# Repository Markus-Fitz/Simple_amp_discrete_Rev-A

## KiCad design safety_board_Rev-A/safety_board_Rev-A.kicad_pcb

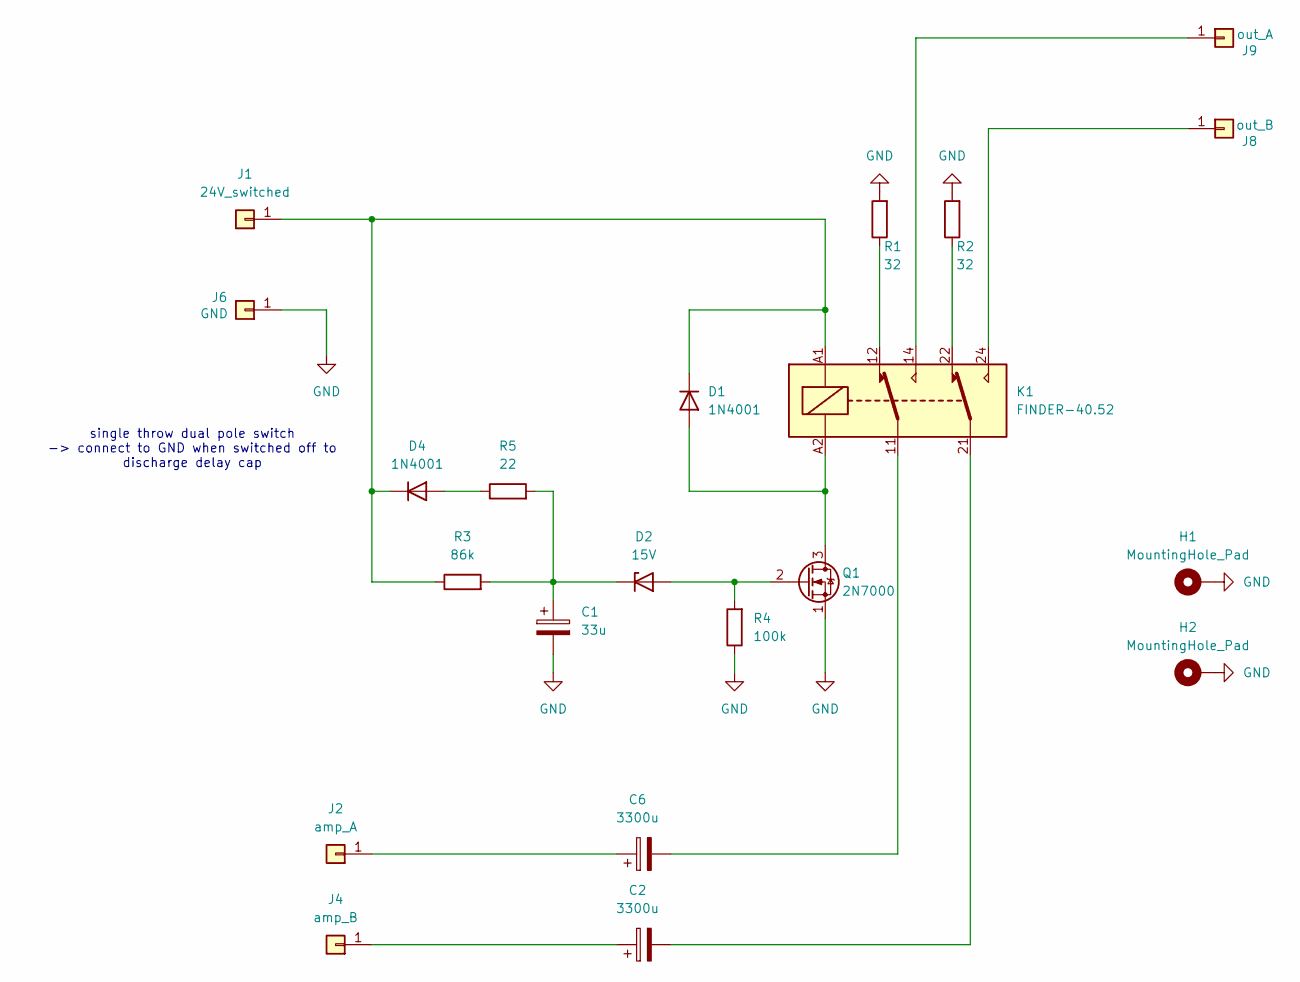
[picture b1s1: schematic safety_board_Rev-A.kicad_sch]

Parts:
C1: 33u; C_Radial_D8.0mm_H11.5mm_P3.50mm
C2, C6: 3300u; CP_Radial_D16.0mm_P7.50mm; MPN UFW1V332MHD
D1, D4: 1N4001; D_DO-41_SOD81_P10.16mm_Horizontal
D2: 15V; D_DO-35_SOD27_P7.62mm_Horizontal
H1, H2: MountingHole_Pad; MountingHole_3.2mm_M3_DIN965_Pad_TopBottom
J1: 24V_switched; TestPoint_THTPad_D3.0mm_Drill1.5mm
J2: amp_A; TestPoint_THTPad_D3.0mm_Drill1.5mm
J4: amp_B; TestPoint_THTPad_D3.0mm_Drill1.5mm
J6: GND; TestPoint_THTPad_D3.0mm_Drill1.5mm
J8: out_B; TestPoint_THTPad_D3.0mm_Drill1.5mm
J9: out_A; TestPoint_THTPad_D3.0mm_Drill1.5mm
K1: FINDER-40.52; Relay_DPDT_Finder_40.52
Q1: 2N7000; TO-92_Inline
R1, R2: 32; R_Axial_DIN0207_L6.3mm_D2.5mm_P10.16mm_Horizontal
R3: 86k; R_Axial_DIN0207_L6.3mm_D2.5mm_P10.16mm_Horizontal
R4: 100k; R_Axial_DIN0207_L6.3mm_D2.5mm_P10.16mm_Horizontal
R5: 22; R_Axial_DIN0207_L6.3mm_D2.5mm_P10.16mm_Horizontal

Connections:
GND: C1.2, H1.1, H2.1, J6.1, Q1.1 (S), R1.2, R2.2, R4.1
unnamed: C2.2, K1.21
unnamed: C6.2, K1.11
unnamed: D1.2 (A), K1.A2, Q1.3 (D)
unnamed: D1.1 (K), D4.1 (K), J1.1, K1.A1, R3.1
unnamed: D2.2 (A), Q1.2 (G), R4.2
unnamed: C1.1, D2.1 (K), R3.2, R5.2
unnamed: D4.2 (A), R5.1
unnamed: C6.1, J2.1
unnamed: C2.1, J4.1
unnamed: J8.1, K1.24
unnamed: J9.1, K1.14
unnamed: K1.12, R1.1
unnamed: K1.22, R2.1

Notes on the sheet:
single throw dual pole switch -> connect to GND when switched off to discharge delay cap

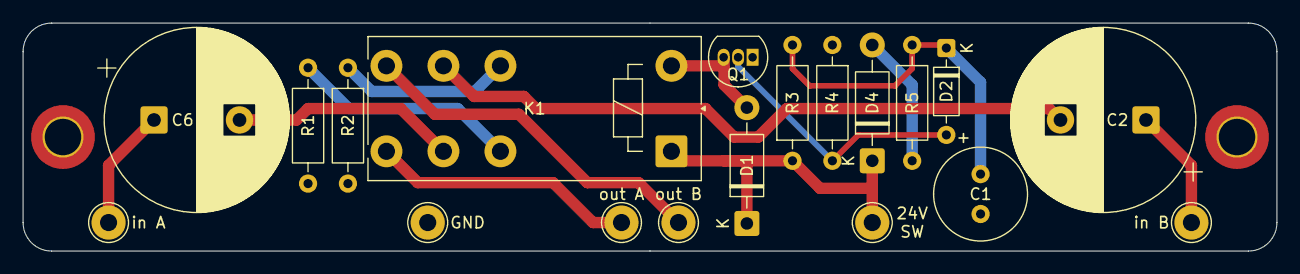
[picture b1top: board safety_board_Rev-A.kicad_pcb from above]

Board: 2 copper layers, 110.0 x 20.0 mm, 21 parts (0 on the bottom side), 14 nets.

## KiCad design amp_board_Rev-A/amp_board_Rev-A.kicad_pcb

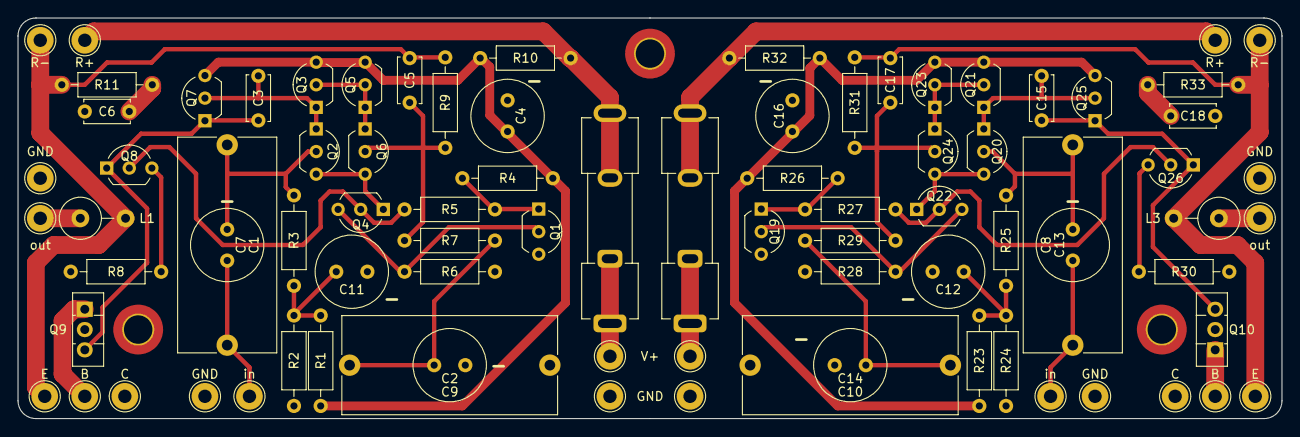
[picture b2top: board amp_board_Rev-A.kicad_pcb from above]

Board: 2 copper layers, 142.0 x 45.0 mm, 87 parts (0 on the bottom side), 41 nets.

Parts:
C1, C2, C4, C11, C12, C13, C14, C16: 33u; C_Radial_D8.0mm_H11.5mm_P3.50mm
C3, C15: 47p; C_Disc_D5.0mm_W2.5mm_P5.00mm
C5, C17: 3.3p; C_Disc_D5.0mm_W2.5mm_P5.00mm
C6, C18: C_sn; C_Disc_D5.0mm_W2.5mm_P5.00mm
C7, C8, C9, C10: 10u_foil; C_Rect_L24.0mm_W10.9mm_P22.50mm_MKT
F1, F2: 2A f; Fuseholder_Clip-5x20mm_Keystone_3512P_Inline_P23.62x7.27mm_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
H1, H2, H3: MountingHole_Pad; MountingHole_3.2mm_M3_DIN965_Pad_TopBottom
J1: in; TestPoint_THTPad_D3.0mm_Drill1.5mm
J2: R_power+; TestPoint_THTPad_D3.0mm_Drill1.5mm
J3: R_power-; TestPoint_THTPad_D3.0mm_Drill1.5mm
J4: MJ2955_E; TestPoint_THTPad_D3.0mm_Drill1.5mm
J5: MJ2955_B; TestPoint_THTPad_D3.0mm_Drill1.5mm
J6: MJ2955_C; TestPoint_THTPad_D3.0mm_Drill1.5mm
J7, J10: V+_in; TestPoint_THTPad_D3.0mm_Drill1.5mm
J8: out; TestPoint_THTPad_D3.0mm_Drill1.5mm
J9, J12: GND; TestPoint_THTPad_D3.0mm_Drill1.5mm
J11: in_GND; TestPoint_THTPad_D3.0mm_Drill1.5mm
J_B1: MJ2955_B; TestPoint_THTPad_D3.0mm_Drill1.5mm
J_C1: MJ2955_C; TestPoint_THTPad_D3.0mm_Drill1.5mm
J_E1: MJ2955_E; TestPoint_THTPad_D3.0mm_Drill1.5mm
J_GND1: in_GND; TestPoint_THTPad_D3.0mm_Drill1.5mm
J_GND2, J_GND3: out_GND; TestPoint_THTPad_D3.0mm_Drill1.5mm
J_R+1: R_power+; TestPoint_THTPad_D3.0mm_Drill1.5mm
J_R-1: R_power-; TestPoint_THTPad_D3.0mm_Drill1.5mm
J_in1: in; TestPoint_THTPad_D3.0mm_Drill1.5mm
J_out1: out; TestPoint_THTPad_D3.0mm_Drill1.5mm
L1, L3: 10u; L_Axial_L11.0mm_D4.5mm_P5.08mm_Vertical_Fastron_MECC
Q1, Q2, Q4, Q6, Q8, Q19, Q20, Q22, Q24, Q26: BC547; TO-92_Inline_Wide
Q3, Q5, Q7, Q21, Q23, Q25: BC557; TO-92_Inline_Wide
Q9, Q10: BD140; TO-126-3_Vertical
R1, R2, R23, R24: 4k7; R_Axial_DIN0207_L6.3mm_D2.5mm_P10.16mm_Horizontal
R3, R25: 42k; R_Axial_DIN0207_L6.3mm_D2.5mm_P10.16mm_Horizontal
R4, R26: 22k; R_Axial_DIN0207_L6.3mm_D2.5mm_P10.16mm_Horizontal
R5, R6, R27, R28: 1k; R_Axial_DIN0207_L6.3mm_D2.5mm_P10.16mm_Horizontal
R7, R29: 10k; R_Axial_DIN0207_L6.3mm_D2.5mm_P10.16mm_Horizontal
R8, R30: 330; R_Axial_DIN0207_L6.3mm_D2.5mm_P10.16mm_Horizontal
R9, R31: 47k; R_Axial_DIN0207_L6.3mm_D2.5mm_P10.16mm_Horizontal
R10, R32: 10; R_Axial_DIN0207_L6.3mm_D2.5mm_P10.16mm_Horizontal
R11, R33: R_sn; R_Axial_DIN0207_L6.3mm_D2.5mm_P10.16mm_Horizontal

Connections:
/channel_l/V+: F2.1, J7.1
/channel_l/V+_filt: C16.1, Q21.3 (E), Q23.3 (E), Q25.3 (E), R23.1, R26.2, R32.1
/channel_l/in+: C8.2, C13.2, Q20.2 (B), R25.2
/channel_l/in-: C17.1, Q24.2 (B), R29.1, R31.1
/channel_r/V+: F1.1, J10.1
/channel_r/V+_filt: C4.1, Q3.3 (E), Q5.3 (E), Q7.3 (E), R1.1, R4.2, R10.1
/channel_r/in+: C1.2, C7.2, Q2.2 (B), R3.2
/channel_r/in-: C5.1, Q6.2 (B), R7.1, R9.1
GND: C2.2, C4.2, C6.2, C9.2, C10.2, C11.2, C12.2, C14.2, C16.2, C18.2, H1.1, H2.1, H3.1, J6.1, J9.1, J11.1, J12.1, J_C1.1, J_GND1.1, J_GND2.1, J_GND3.1, Q1.3 (E), Q9.2 (C), Q10.2 (C), Q19.3 (E), R2.2, R6.2, R8.2, R24.2, R28.2, R30.2
unnamed: C2.1, C9.1, R7.2
unnamed: C6.1, R11.2
unnamed: C10.1, C14.1, R29.2
unnamed: C11.1, R1.2, R2.1, R3.1
unnamed: C12.1, R23.2, R24.1, R25.1
unnamed: C18.1, R33.2
unnamed: C1.1, C7.1, J1.1
unnamed: F1.2, J2.1, R10.2
unnamed: C5.2, J3.1, J4.1, L1.2, R9.2, R11.1
unnamed: J5.1, Q9.1 (E)
unnamed: J8.1, L1.1
unnamed: J_B1.1, Q10.1 (E)
unnamed: C17.2, J_E1.1, J_R-1.1, L3.2, R31.2, R33.1
unnamed: F2.2, J_R+1.1, R32.2
unnamed: C8.1, C13.1, J_in1.1
unnamed: J_out1.1, L3.1
unnamed: Q1.2 (B), Q4.3 (E), R6.1
unnamed: Q1.1 (C), R4.1, R5.1
unnamed: C3.1, Q2.1 (C), Q3.1 (C), Q7.2 (B)
unnamed: Q2.3 (E), Q4.1 (C), Q6.3 (E)
unnamed: Q3.2 (B), Q5.1 (C), Q5.2 (B), Q6.1 (C)
unnamed: Q4.2 (B), Q8.2 (B), R5.2
unnamed: C3.2, Q7.1 (C), Q8.1 (C), Q9.3 (B)
unnamed: Q8.3 (E), R8.1
unnamed: C15.2, Q10.3 (B), Q25.1 (C), Q26.1 (C)
unnamed: Q19.2 (B), Q22.3 (E), R28.1
unnamed: Q19.1 (C), R26.1, R27.1
unnamed: C15.1, Q20.1 (C), Q21.1 (C), Q25.2 (B)
unnamed: Q20.3 (E), Q22.1 (C), Q24.3 (E)
unnamed: Q21.2 (B), Q23.1 (C), Q23.2 (B), Q24.1 (C)
unnamed: Q22.2 (B), Q26.2 (B), R27.2
unnamed: Q26.3 (E), R30.1

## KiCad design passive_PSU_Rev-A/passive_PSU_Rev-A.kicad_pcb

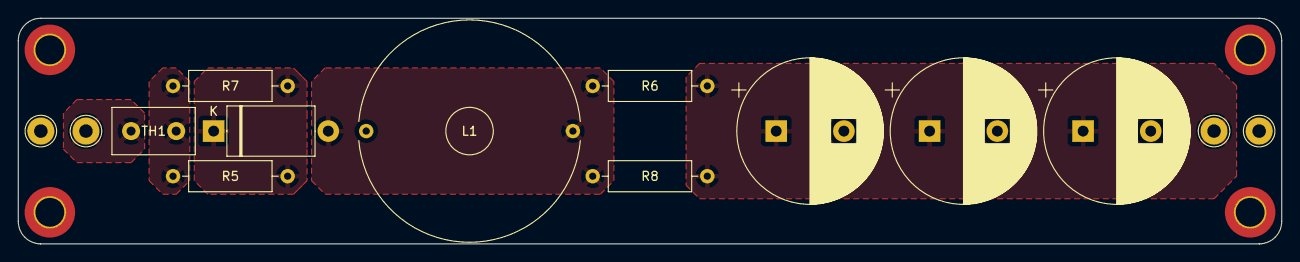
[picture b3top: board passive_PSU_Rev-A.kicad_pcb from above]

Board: 2 copper layers, 140.0 x 25.0 mm, 18 parts (0 on the bottom side), 6 nets, no tracks yet.

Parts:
C4, C5, C6: 3300u; CP_Radial_D16.0mm_P7.50mm
D1: D; D_DO-27_P12.70mm_Horizontal
H1, H2, H3, H4: MountingHole_Pad; MountingHole_3.2mm_M3_DIN965_Pad_TopBottom
J1, J2, J3, J4: Conn_01x01; TestPoint_THTPad_D3.0mm_Drill1.5mm
L1: 4.7m; L_Radial_D24.4mm_P22.90mm_Murata_1400series
R5, R6, R7, R8: 4.7 2W; R_Axial_DIN0309_L9.0mm_D3.2mm_P12.70mm_Horizontal
TH1: inrush_limit; C_Disc_D9.0mm_W5.0mm_P5.00mm

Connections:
GND: C4.2, C5.2, C6.2, H1.1, H2.1, H3.1, H4.1, J2.1, J4.1
unnamed: D1.2 (A), L1.2, R6.1, R8.1
unnamed: D1.1 (K), L1.1, R5.2, R7.2
unnamed: J1.1, TH1.1
unnamed: C4.1, C5.1, C6.1, J3.1, R6.2, R8.2
unnamed: R5.1, R7.1, TH1.2

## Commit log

2025-06-10 Initial commit.
2025-06-10 Added local files.
2025-06-14 Added images for the turn-on delay board, visual modifications to schematic.
